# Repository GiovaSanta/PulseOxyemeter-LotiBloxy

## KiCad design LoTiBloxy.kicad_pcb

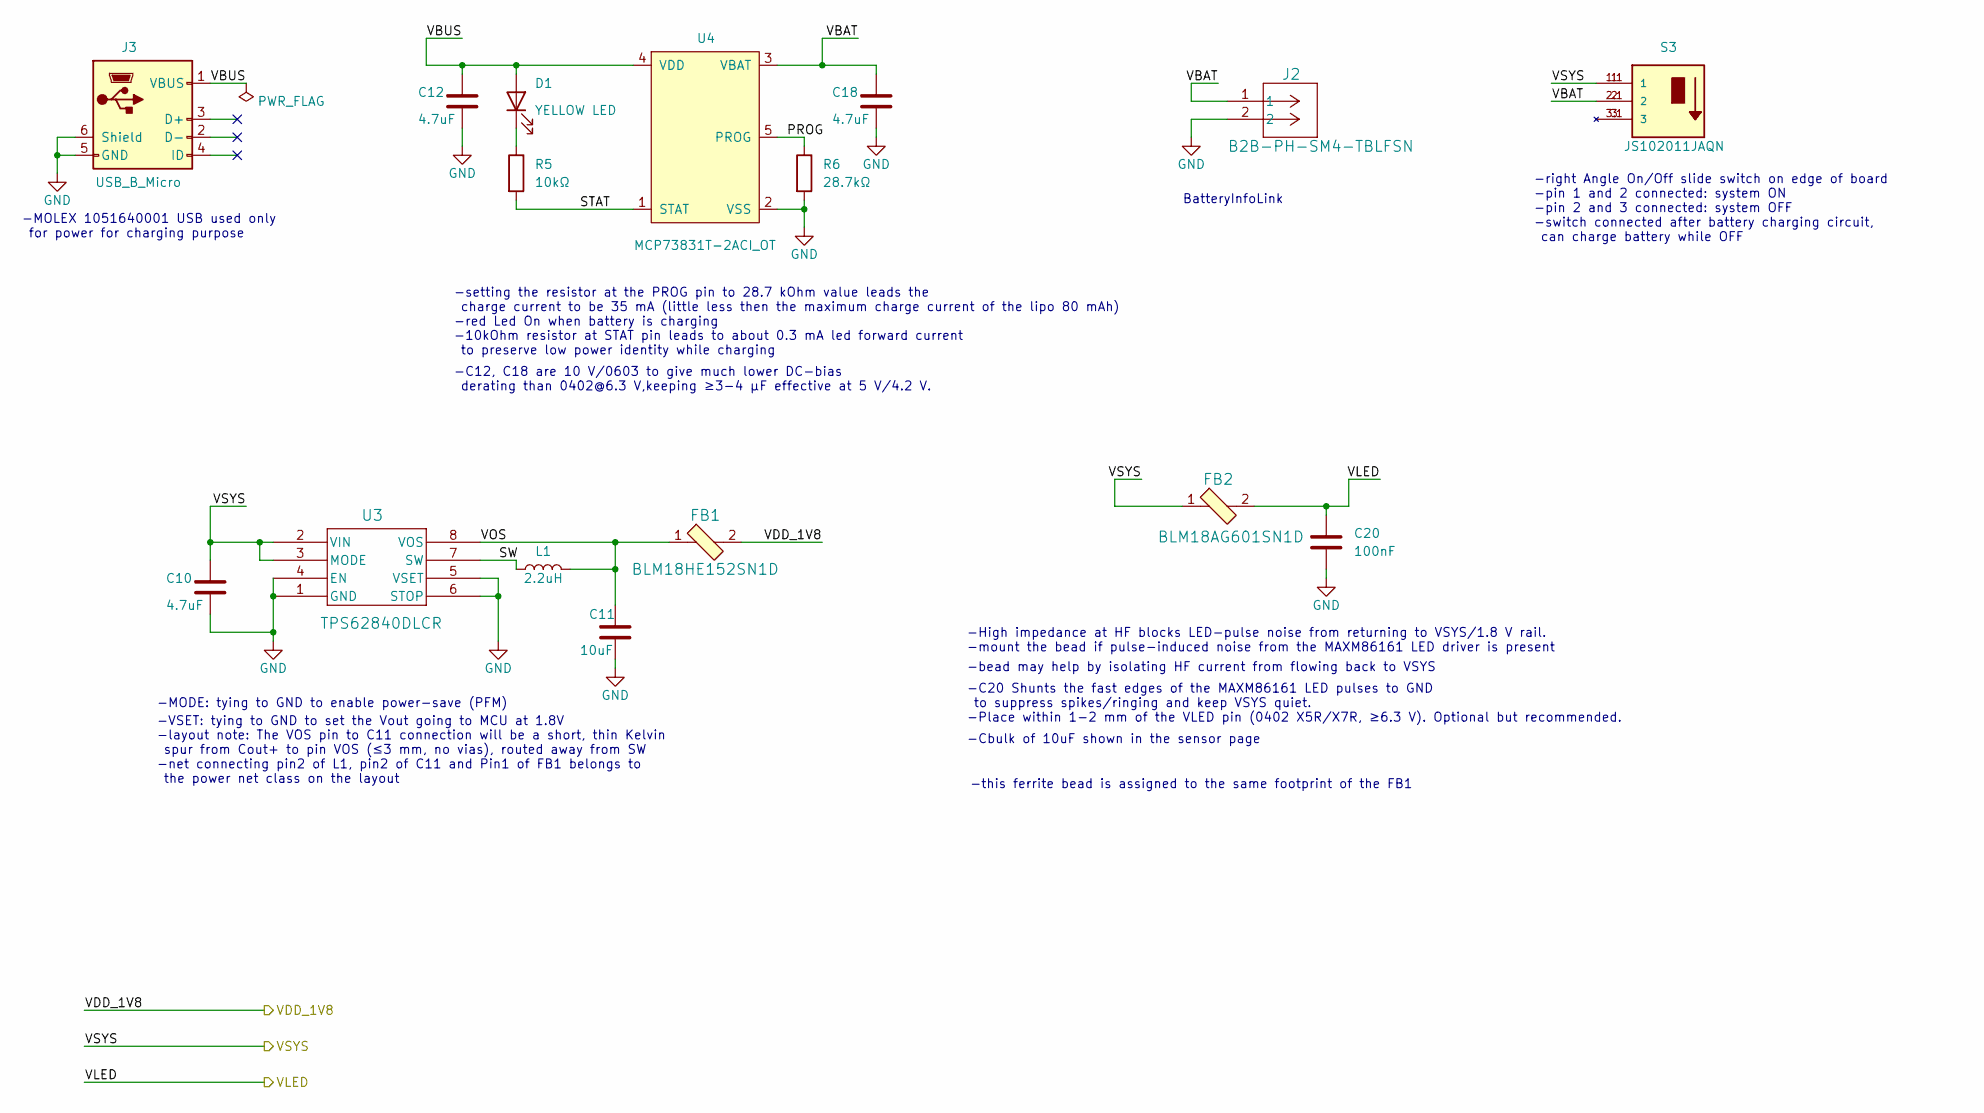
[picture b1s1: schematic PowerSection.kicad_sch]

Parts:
C10, C12, C18: 4.7uF; C_0603_1608Metric; MPN CC0603KRX5R6BB475
C11: 10uF; C_0603_1608Metric; MPN GRM188R60J106ME47D
C20: 100nF; C_0402_1005Metric; MPN GRM155R70J104KA01D
D1: YELLOW LED; LED_SML-P12UT_ROM; MPN SML-P11YTT86
FB1: BLM18HE152SN1D; IND_BLM18_0603_MUR; MPN BLM18HE152SN1D; Digi-Key_PN 490-5216-1-ND
FB2: BLM18AG601SN1D; IND_BLM18_0603_MUR; MPN BLM18AG601SN1D; Digi-Key_PN 490-1014-1-ND
J2: B2B-PH-SM4-TBLFSN; CONN_S2B-PH-SM4-TB_JST; MPN B2B-PH-SM4-TB
J3: USB_B_Micro; CON00906_5_MOL; MPN 1051640001
L1: 2.2uH; L_0805_2012M_Murata-LQM21PN; MPN LQM21PN2R2NGCD
R5: 10kΩ; R_0402_1005Metric; MPN RMCF0402FT10K0
R6: 28.7kΩ; R_0402_1005Metric; MPN RMCF0402FT28K7
S3: JS102011JAQN; SW_JS102011JAQN; PARTREV 29 June 16
U3: TPS62840DLCR; VSON8_2P1X1P6_TEX; MPN TPS62840DLCR
U4: MCP73831T-2ACI_OT; mcp73831T_SOT-23-5; MPN MCP73831T-2ACI/OT; Digi-Key_PN MCP73831T-2ACI/OTCT-ND

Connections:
/PowerSection/PROG: R6.1, U4.5 (PROG)
/PowerSection/STAT: R5.2, U4.1 (STAT)
/PowerSection/SW: L1.1, U3.7 (SW)
/PowerSection/VBAT: C18.1, J2.1, S3.2, S3.2.1 (2), U4.3 (VBAT)
/PowerSection/VBUS: C12.1, D1.2 (A), J3.1 (VBUS), U4.4 (VDD)
/PowerSection/VOS: C11.1, FB1.1, L1.2, U3.8 (VOS)
/VDD_1V8: FB1.2; also elsewhere on the board
/VLED: C20.1, FB2.2; also elsewhere on the board
/VSYS: C10.1, FB2.1, S3.1, S3.1.1 (1), U3.2 (VIN), U3.3 (MODE); also elsewhere on the board
GND: C10.2, C11.2, C12.2, C18.2, C20.2, J2.2, J3.5 (GND), J3.6 (Shield), R6.2, U3.1 (GND), U3.4 (EN), U3.5 (VSET), U3.6 (STOP), U4.2 (VSS); also elsewhere on the board
unnamed: D1.1 (K), R5.1

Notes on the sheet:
-VSET: tying to GND to set the Vout going to MCU at 1.8V
-setting the resistor at the PROG pin to 28.7 kOhm value leads the charge current to be 35 mA (little less then the maximum charge current of the lipo 80 mAh) -red Led On when battery is charging
BatteryInfoLink
-C20 Shunts the fast edges of the MAXM86161 LED pulses to GND to suppress spikes/ringing and keep VSYS quiet. -Place within 1-2 mm of the VLED pin (0402 X5R/X7R, ≥6.3 V). Optional but recommended.
-Cbulk of 10uF shown in the sensor page
-10kOhm resistor at STAT pin leads to about 0.3 mA led forward current to preserve low power identity while charging
-C12, C18 are 10 V/0603 to give much lower DC-bias derating than 0402@6.3 V,keeping ≥3-4 µF effective at 5 V/4.2 V.
-right Angle On/Off slide switch on edge of board -pin 1 and 2 connected: system ON -pin 2 and 3 connected: system OFF -switch connected after battery charging circuit, can charge battery while OFF
-MOLEX 1051640001 USB used only for power for charging purpose
-this ferrite bead is assigned to the same footprint of the FB1
-bead may help by isolating HF current from flowing back to VSYS
-MODE: tying to GND to enable power-save (PFM)
-layout note: The VOS pin to C11 connection will be a short, thin Kelvin spur from Cout+ to pin VOS (≤3 mm, no vias), routed away from SW -net connecting pin2 of L1, pin2 of C11 and Pin1 of FB1 belongs to the power net class on the layout
-High impedance at HF blocks LED-pulse noise from returning to VSYS/1.8 V rail. -mount the bead if pulse-induced noise from the MAXM86161 LED driver is present

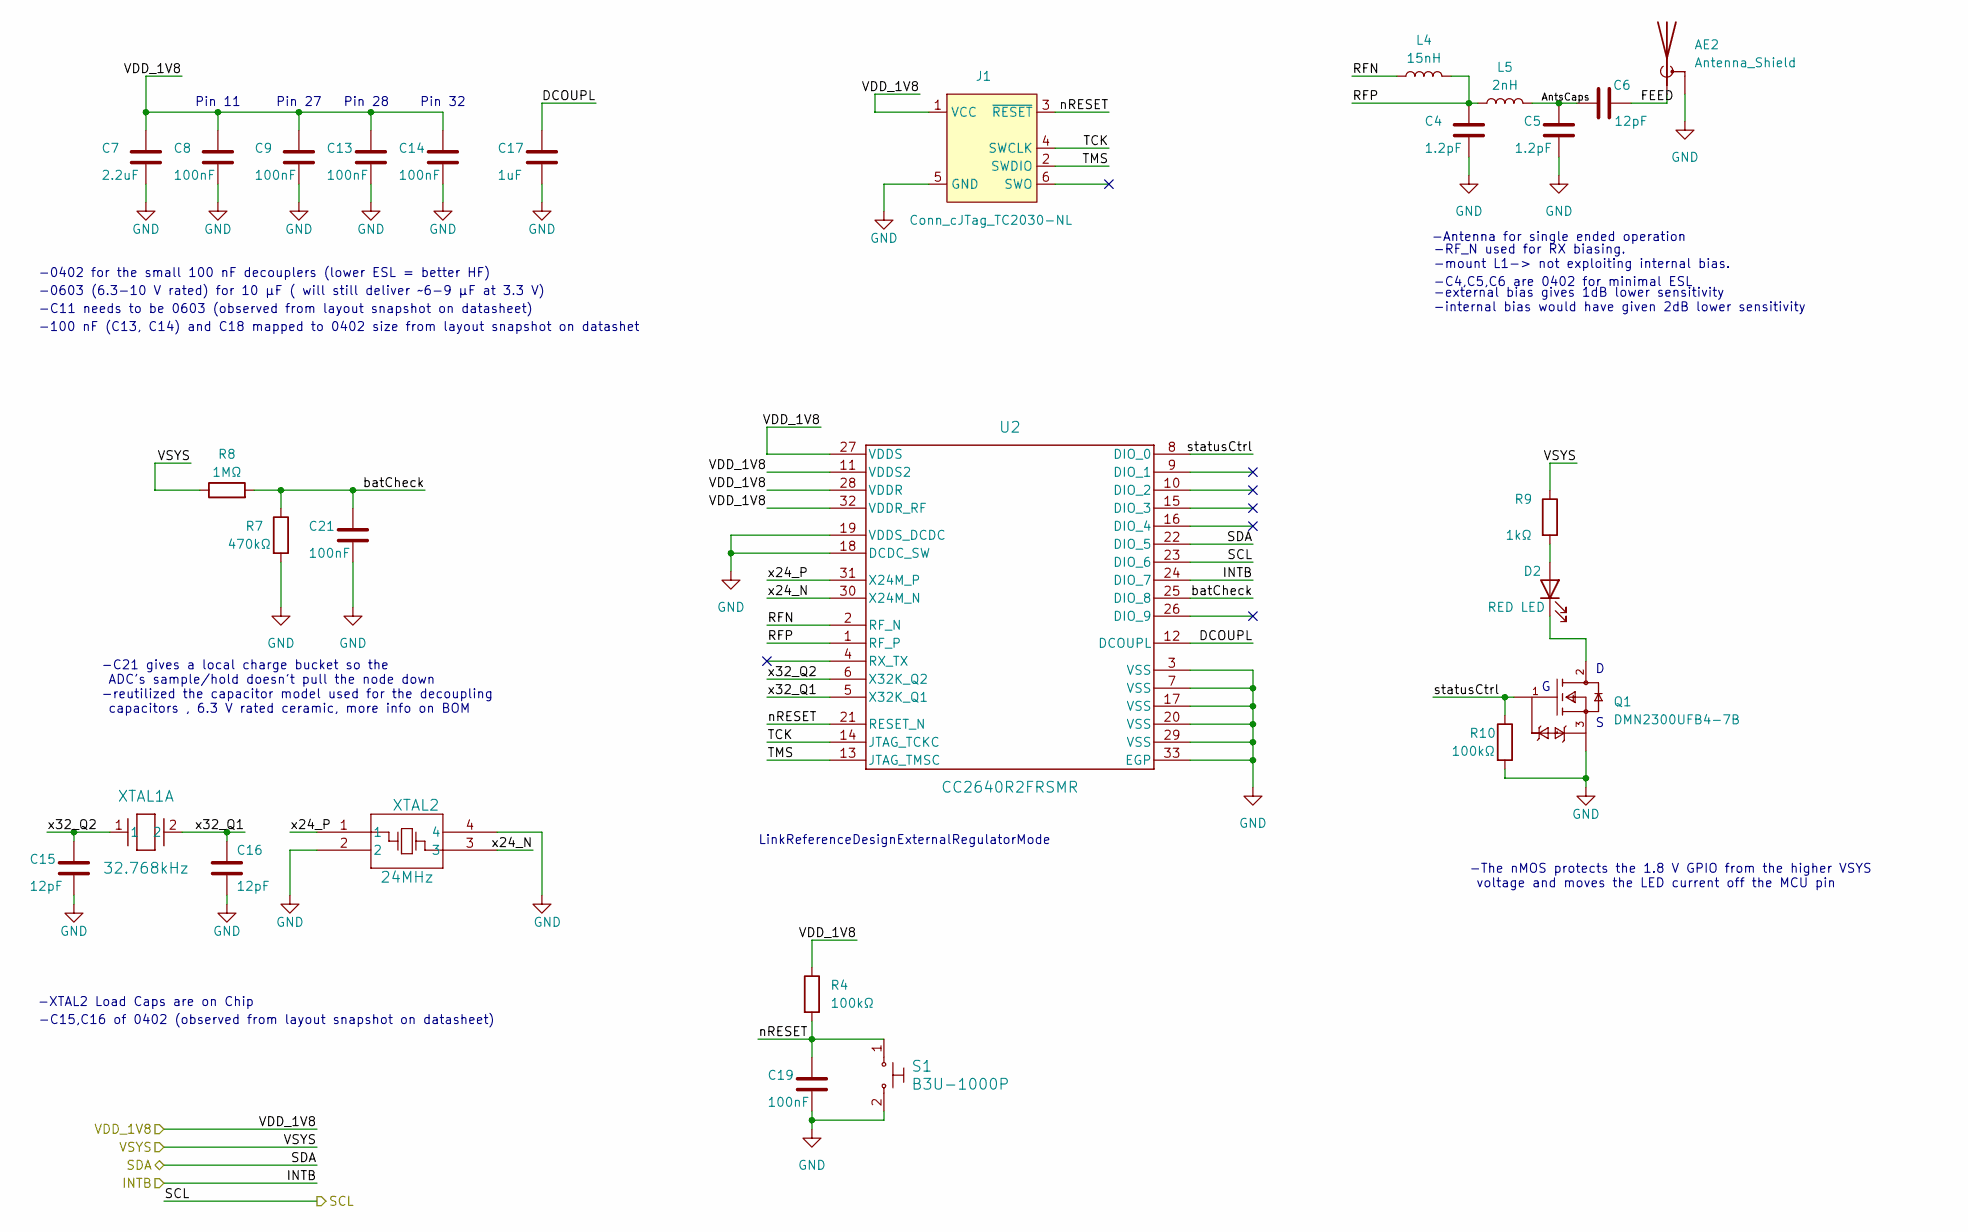
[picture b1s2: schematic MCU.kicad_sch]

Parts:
AE2: Antenna_Shield; Texas_SWRA117D_2.4GHz_Left
C4, C5: 1.2pF; C_0402_1005Metric; MPN GRM1555C1H1R2BA01D
C6, C15, C16: 12pF; C_0402_1005Metric; MPN QSCF500Q120J1GV001T
C7: 2.2uF; C_0402_1005Metric; MPN GRM155R60J225KE95D
C8, C9, C13, C14, C19, C21: 100nF; C_0402_1005Metric; MPN GRM155R70J104KA01D
C17: 1uF; C_0402_1005Metric; MPN CC0402KRX5R6BB105
D2: RED LED; LED_SML-P12UT_ROM; MPN SML-P11VTT86
J1: Conn_cJTag_TC2030-NL; Tag-Connect_TC2030-IDC-NL_2x03_P1.27mm_Vertical
L4: 15nH; L_0402_1005M_Murata-LQG15HS; MPN LQG15HS15NJ02D
L5: 2nH; L_0402_1005M_Murata-LQG15HS; MPN LQG15HS2N0S02D
Q1: DMN2300UFB4-7B; Diodes_Inc.-X2-DFN1006-3-04_2017-0-MFG; mouser part number 522-DMN2300UFB4-7B; digikey description MOSFET N-CH 20V 1.3A 3DFN
R4, R10: 100kΩ; R_0402_1005Metric; MPN RMCF0402FT100K
R7: 470kΩ; R_0402_1005Metric; MPN RMCF0402FT470K
R8: 1MΩ; R_0402_1005Metric; MPN CRGCQ0402F1M0
R9: 1kΩ; R_0402_1005Metric; MPN RMCF0402FT1K00
S1: B3U-1000P; Switch_Tactile_SMD_B3U-1000P; MPN B3U-1000P; Digi-Key_PN SW1020CT-ND
U2: CC2640R2FRSMR; MCU_CC2640R2F_RSM0032B; MPN CC2640R2FRSM
XTAL1: 32.768kHz; XTAL_SC-20S_EPS; MPN SC20S-12.5PF20PPM
XTAL2: 24MHz; ECS-160-8-36-RHN-TR_ECS; MPN ECS-240-8-36-RWN-TR

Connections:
/INTB: U2.24 (DIO_7); also elsewhere on the board
/MCU/AntsCaps: C5.1, C6.1, L5.2
/MCU/DCOUPL: C17.1, U2.12 (DCOUPL)
/MCU/FEED: AE2.1 (A), C6.2
/MCU/RFN: L4.1, U2.2 (RF_N)
/MCU/RFP: C4.1, L4.2, L5.1, U2.1 (RF_P)
/MCU/TCK: J1.4 (SWCLK), U2.14 (JTAG_TCKC)
/MCU/TMS: J1.2 (SWDIO), U2.13 (JTAG_TMSC)
/MCU/batCheck: C21.1, R7.1, R8.2, U2.25 (DIO_8)
/MCU/nRESET: C19.1, J1.3 (~RESET), R4.2, S1.1, U2.21 (RESET_N)
/MCU/statusCtrl: Q1.1 (G), R10.1, U2.8 (DIO_0)
/MCU/x24_N: U2.30 (X24M_N), XTAL2.3
/MCU/x24_P: U2.31 (X24M_P), XTAL2.1
/MCU/x32_Q1: C16.1, U2.5 (X32K_Q1), XTAL1.2
/MCU/x32_Q2: C15.1, U2.6 (X32K_Q2), XTAL1.1
/SCL: U2.23 (DIO_6); also elsewhere on the board
/SDA: U2.22 (DIO_5); also elsewhere on the board
/VDD_1V8: C7.1, C8.1, C9.1, C13.1, C14.1, J1.1 (VCC), R4.1, U2.11 (VDDS2), U2.27 (VDDS), U2.28 (VDDR), U2.32 (VDDR_RF); also elsewhere on the board
/VSYS: R8.1, R9.1; also elsewhere on the board
GND: AE2.2 (Shield), C4.2, C5.2, C7.2, C8.2, C9.2, C13.2, C14.2, C15.2, C16.2, C17.2, C19.2, C21.2, J1.5 (GND), Q1.3 (S), R7.2, R10.2, S1.2, U2.3 (VSS), U2.7 (VSS), U2.17 (VSS), U2.18 (DCDC_SW), U2.19 (VDDS_DCDC), U2.20 (VSS), U2.29 (VSS), U2.33 (EGP), XTAL2.2, XTAL2.4; also elsewhere on the board
unnamed: D2.2 (A), R9.2
unnamed: D2.1 (K), Q1.2 (D)

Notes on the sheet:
-RF_N used for RX biasing. -mount L1-> not exploiting internal bias.
Pin 28
-C11 needs to be 0603 (observed from layout snapshot on datasheet)
LinkReferenceDesignExternalRegulatorMode
-100 nF (C13, C14) and C18 mapped to 0402 size from layout snapshot on datashet
-external bias gives 1dB lower sensitivity -internal bias would have given 2dB lower sensitivity
-C4,C5,C6 are 0402 for minimal ESL
Pin 32
-The nMOS protects the 1.8 V GPIO from the higher VSYS voltage and moves the LED current off the MCU pin
Pin 27
-XTAL2 Load Caps are on Chip
-C21 gives a local charge bucket so the ADC's sample/hold doesn't pull the node down -reutilized the capacitor model used for the decoupling capacitors , 6.3 V rated ceramic, more info on BOM
-0402 for the small 100 nF decouplers (lower ESL = better HF)
Pin 11
-C15,C16 of 0402 (observed from layout snapshot on datasheet)
-Antenna for single ended operation
-0603 (6.3-10 V rated) for 10 µF ( will still deliver ~6-9 µF at 3.3 V)

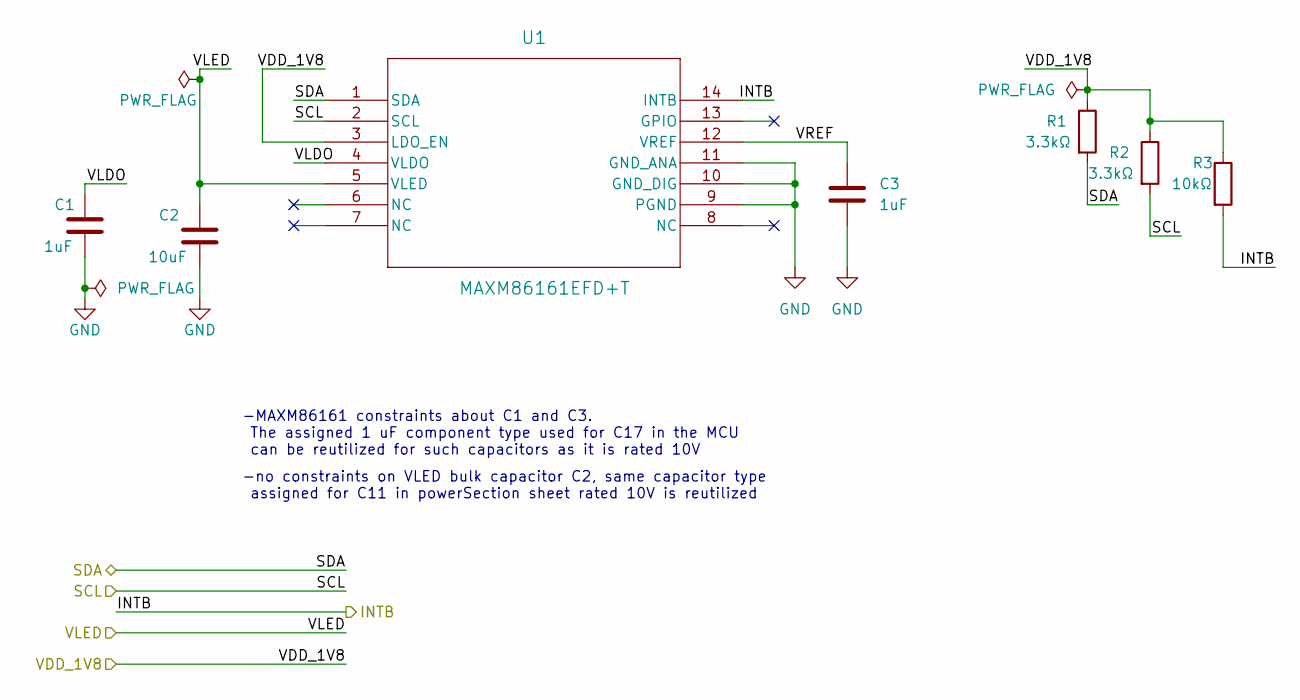
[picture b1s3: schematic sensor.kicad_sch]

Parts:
C1, C3: 1uF; C_0402_1005Metric; MPN CC0402KRX5R6BB105
C2: 10uF; C_0603_1608Metric; MPN GRM188R60J106ME47D
R1, R2: 3.3kΩ; R_0402_1005Metric; MPN RMCF0402FT3K30
R3: 10kΩ; R_0402_1005Metric; MPN RMCF0402FT10K0
U1: MAXM86161EFD+T; ul_MAXM86161EFD-T; MPN MAXM86161EFD+T

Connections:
/INTB: R3.2, U1.14 (INTB); also elsewhere on the board
/SCL: R2.2, U1.2 (SCL); also elsewhere on the board
/SDA: R1.2, U1.1 (SDA); also elsewhere on the board
/VDD_1V8: R1.1, R2.1, R3.1, U1.3 (LDO_EN); also elsewhere on the board
/VLED: C2.1, U1.5 (VLED); also elsewhere on the board
/sensor/VLDO: C1.1, U1.4 (VLDO)
/sensor/VREF: C3.1, U1.12 (VREF)
GND: C1.2, C2.2, C3.2, U1.9 (PGND), U1.10 (GND_DIG), U1.11 (GND_ANA); also elsewhere on the board

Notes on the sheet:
-MAXM86161 constraints about C1 and C3. The assigned 1 uF component type used for C17 in the MCU can be reutilized for such capacitors as it is rated 10V
-no constraints on VLED bulk capacitor C2, same capacitor type assigned for C11 in powerSection sheet rated 10V is reutilized

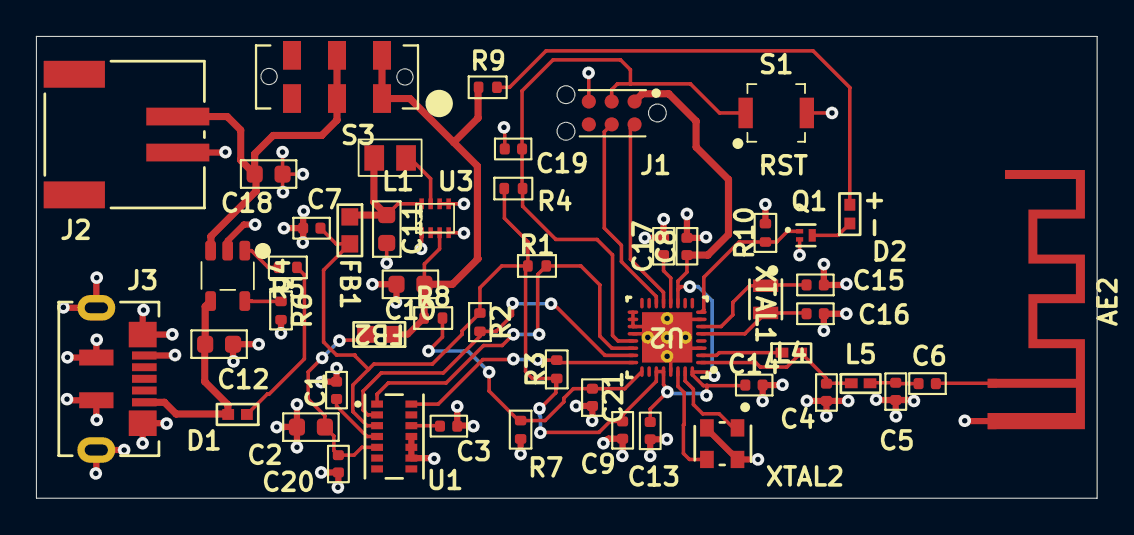
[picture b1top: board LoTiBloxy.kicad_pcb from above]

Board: 2 copper layers, 58.9 x 25.7 mm, 51 parts (0 on the bottom side), 32 nets.

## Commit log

2025-08-18 starting slideset containing main components needed
2025-08-22 finalized a first version of the sensor sheet, need still to perform ERC check on the proposed sensor sheet. started creating the MCU hierechical sheet
2025-08-27 first finished schematic version of the MCU as well as sensor. starting out with schematic of the power related components
2025-08-30 done with first version PowerSection of LoTiBloxy plus MCU plus sensor sheets. still have to add meaningfull comments to all schematic components. still have to make sure every symbol is associated t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
2025-09-01 finished associating each component of each sheet of schematic to relative footprint. filled in first version field for BOM. Provided organized hierechical level directories for all the datasheets fo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
2025-09-02 ERC step done. most important errors and warnings resolved (the ones about unspecified pins etcetra). with the occasion have done also the checking of the symbols of each component to make sure of co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
2025-09-07 finished layout, associated 3d models for the components, drc ran with no errors. fixed foorprints and their individaul pad dimensions (solder mask layer related, copper layer related and paste mask 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
